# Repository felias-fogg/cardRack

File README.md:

# An IoT Card Rack: cardRack

This is a project description showing how to build a 3D-printed card rack that signals how many slots are used over LTE-M. 

### Hardware

The IoT rack uses the IR sensors APDS-9930 for presence sensing and the AVR-IoT Cell Mini board EV70N78A by Microchip as the controller and LTE-M board. Since the sensors use all the same I2C address, they have to be on separate I2C buses. However, all in all, the hardware is very minimal, as one can see in the Fritzing sketch below. The Feather board is actually the mentioned EV70N78A board and not the Feather 328P. Since they have identical pin assignments and there is no Fritzing part for the former one,  I used the latter one.

While the initial version was built on a Featherwing doubler, which looks quite ugly, I have now created a PCB. The KiCAD design data can be found in the [pcb](pcb) directory. 

### Software

The software is quite simple. An interrupt is triggered if a card is removed or inserted. Then, the sensors are polled to check the number of used slots. Finally, a short message is sent via an HTTPS POST command to a webserver, where a CGI script stores the number of occupied slots. One can use the stored number in a Javascript script to display it on a web page. 

To monitor that everything is working, the AVR chip is woken up every 2 hours, and a message with the number of occupied slots is sent. If the last message received is over 3 hours old, the information will no longer be considered valid.

### 3D Print Data

The 3D print data for the physical card rack can be found on [printables.com](https://www.printables.com/model/1051824-iot-card-rack-badge-holder).

### Folders

The repository contains the following folders:
* [IoTRack](IoTRack): The Arduino sketch
* [pics](pics): Some photos
* [schematic](schematic): A Fritzing schematic of the electronics
* [web](web): CGI script, an example bash script to trigger the CGI script, and an example web page 
* [pcb](pcb): KiCAD design files

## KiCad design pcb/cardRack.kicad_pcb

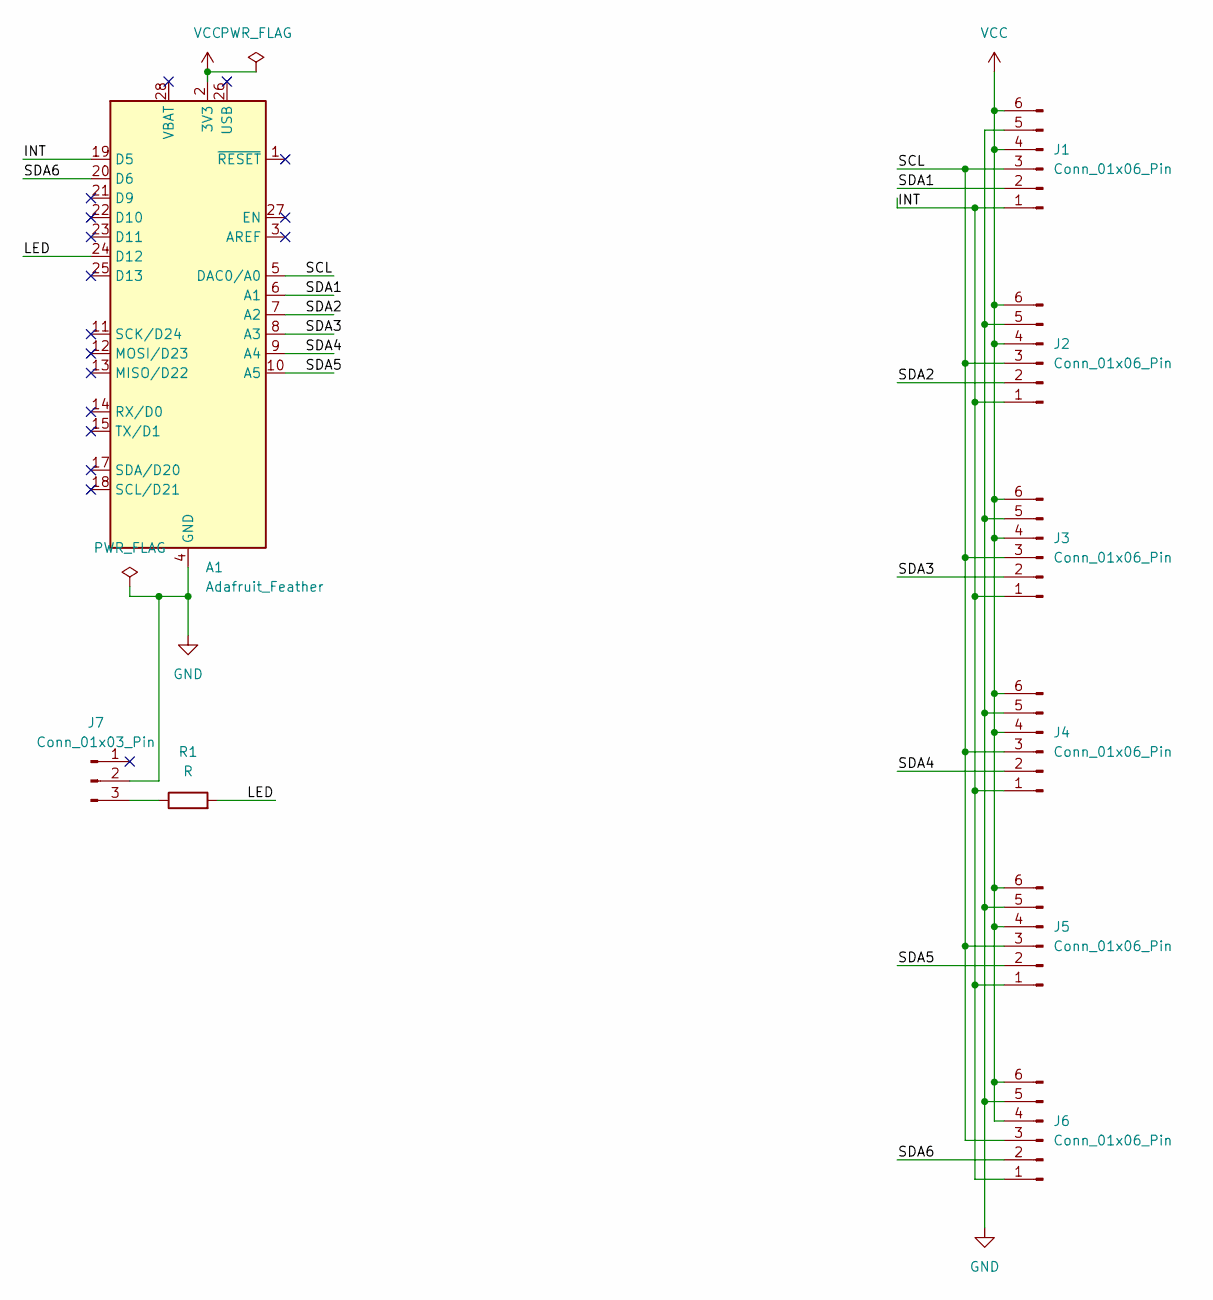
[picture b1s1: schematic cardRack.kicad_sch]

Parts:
A1: Adafruit_Feather
J1, J2, J3, J4, J5, J6: Conn_01x06_Pin; PinHeader_1x06_P2.54mm_Vertical
J7: Conn_01x03_Pin; PinHeader_1x03_P2.54mm_Vertical
R1: R; R_1206_3216Metric_Pad1.30x1.75mm_HandSolder

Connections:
/INT: A1.19 (D5), J1.1, J2.1, J3.1, J4.1, J5.1, J6.1
/LED: A1.24 (D12), R1.2
/SCL: A1.5 (DAC0/A0), J1.3, J2.3, J3.3, J4.3, J5.3, J6.3
/SDA1: A1.6 (A1), J1.2
/SDA2: A1.7 (A2), J2.2
/SDA3: A1.8 (A3), J3.2
/SDA4: A1.9 (A4), J4.2
/SDA5: A1.10 (A5), J5.2
/SDA6: A1.20 (D6), J6.2
GND: A1.4 (GND), A1.16 (GND), J1.5, J2.5, J3.5, J4.5, J5.5, J6.5, J7.2
unnamed: J7.3, R1.1
VCC: A1.2 (3V3), J1.4, J1.6, J2.4, J2.6, J3.4, J3.6, J4.4, J4.6, J5.4, J5.6, J6.4, J6.6

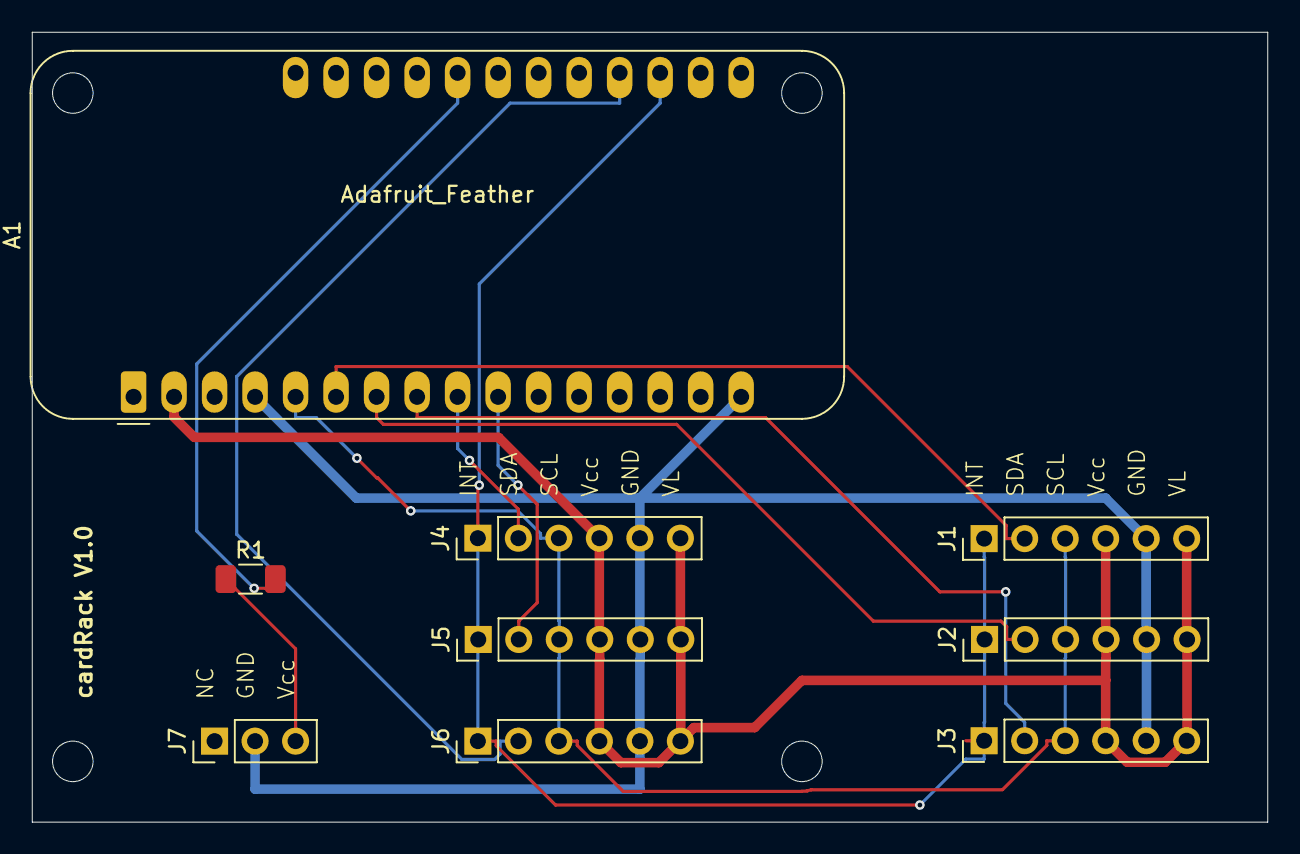
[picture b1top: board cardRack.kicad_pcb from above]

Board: 2 copper layers, 77.5 x 49.5 mm, 9 parts (0 on the bottom side), 12 nets.

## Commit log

2023-12-27 Fritzing schematic added
2023-12-27 readme update
2023-12-27 Picture and readme update
2023-12-28 web interface done
2023-12-29 Web interface slightly adjusted
2024-05-31 V0.2.0
2024-05-31 V0.2.1
2024-06-01 V0.3.0
2024-06-01 V0.3.1
2024-06-02 V0.3.2
2024-06-02 V0.9.0
2024-06-03 V0.9.2
2024-06-04 V0.9.3
2024-06-05 V0.9.4
2024-10-14 0.9.4
2024-10-27 Readme + Fritzing
2024-11-28 V1.0.0
